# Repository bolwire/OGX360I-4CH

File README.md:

This project builds on the original OGX360 by Ryzee119: https://github.com/Ryzee119/ogx360/

The information provided in this repo is for informational purposes only.

The ATMEGA32U4 chips will need to be programmed with the arduino bootloader before they are put on the PCB. One option may be to remove the chips
from an arduino and transplant them.

Please respect the license files found within this project. What we do, and the joy we gain from that would not be possible without those who shared the
information with us to start with. Please respect and honor that by doing the same with any works derived from this or other projects linked to in this repo.

Also my spelling sucks, so I apologize for any type-ohs that exist.

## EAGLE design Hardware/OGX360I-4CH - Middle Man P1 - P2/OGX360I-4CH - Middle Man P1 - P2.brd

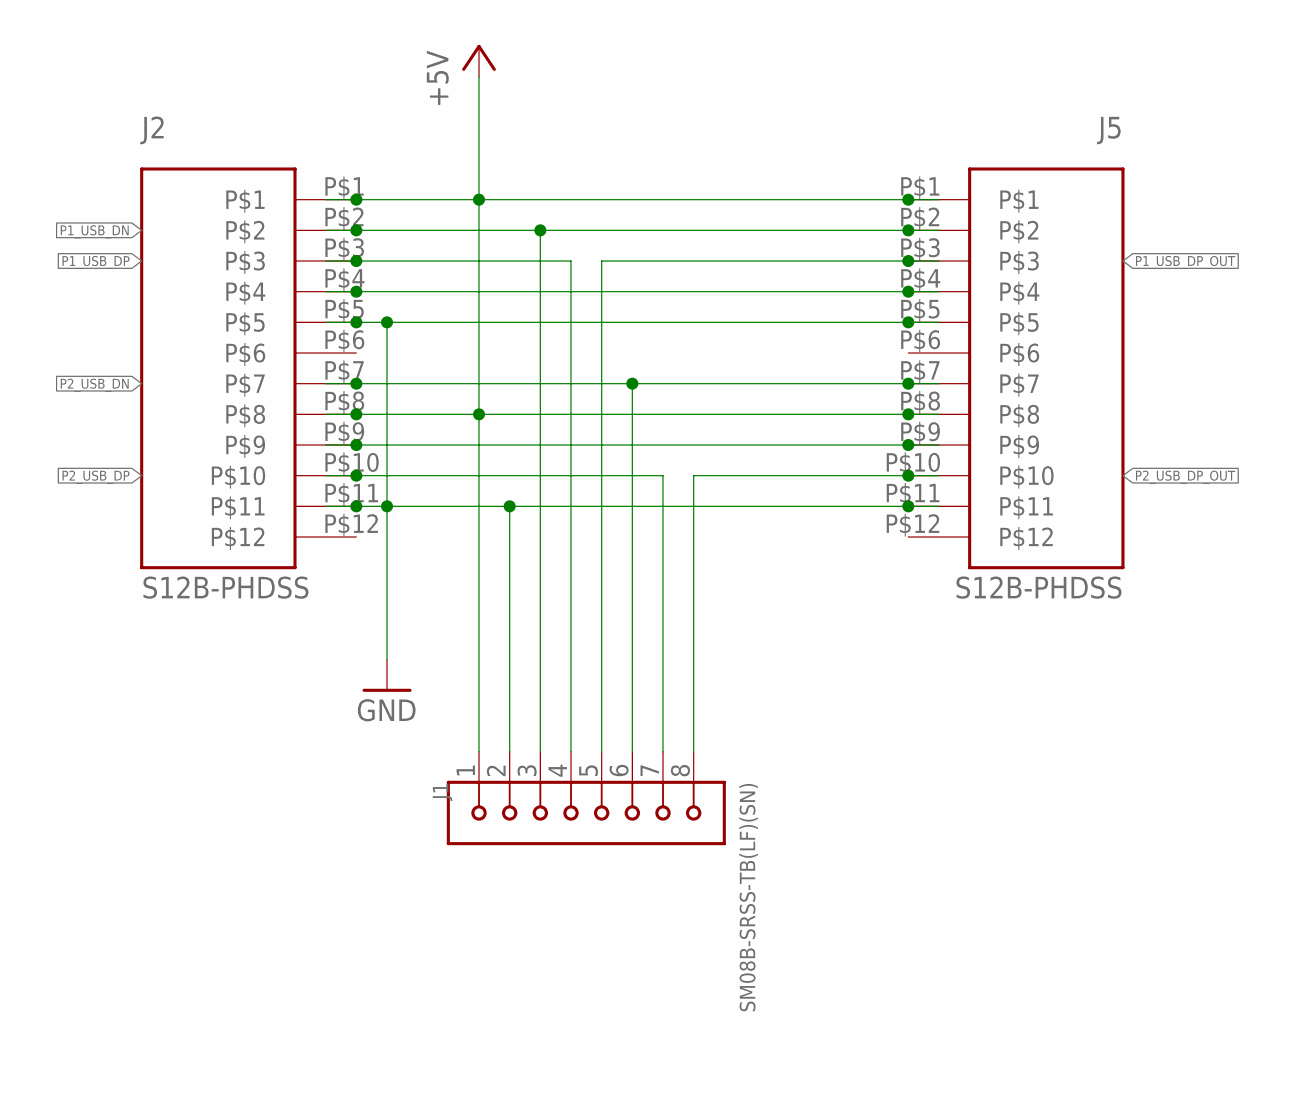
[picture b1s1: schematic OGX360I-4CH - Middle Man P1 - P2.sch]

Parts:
J1: SM08B-SRSS-TB(LF)(SN); JST_SM08B-SRSS-TB(LF)(SN)
J2, J5: S12B-PHDSS

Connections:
+5V: J1.1, J2.P$1, J2.P$8, J5.P$1, J5.P$8
GND: J1.2, J2.P$5, J2.P$11, J5.P$5, J5.P$11
unnamed: J2.P$4, J5.P$4
unnamed: J2.P$9, J5.P$9
P1_USB_DN: J1.3, J2.P$2, J5.P$2
P1_USB_DP: J1.4, J2.P$3
P1_USB_DP_OUT: J1.5, J5.P$3
P2_USB_DN: J1.6, J2.P$7, J5.P$7
P2_USB_DP: J1.7, J2.P$10
P2_USB_DP_OUT: J1.8, J5.P$10

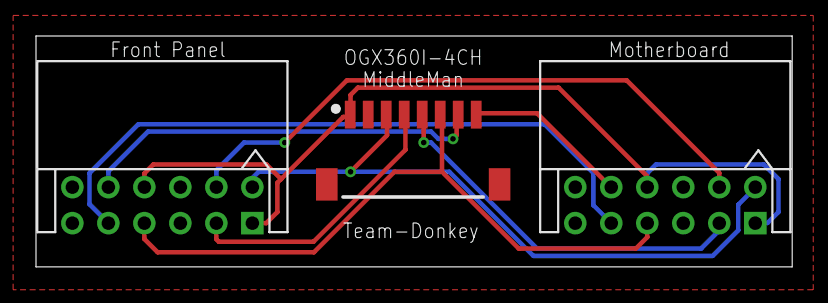
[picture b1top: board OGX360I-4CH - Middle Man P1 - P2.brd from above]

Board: 2 copper layers, 42.0 x 12.8 mm, 3 parts (0 on the bottom side), 10 nets.

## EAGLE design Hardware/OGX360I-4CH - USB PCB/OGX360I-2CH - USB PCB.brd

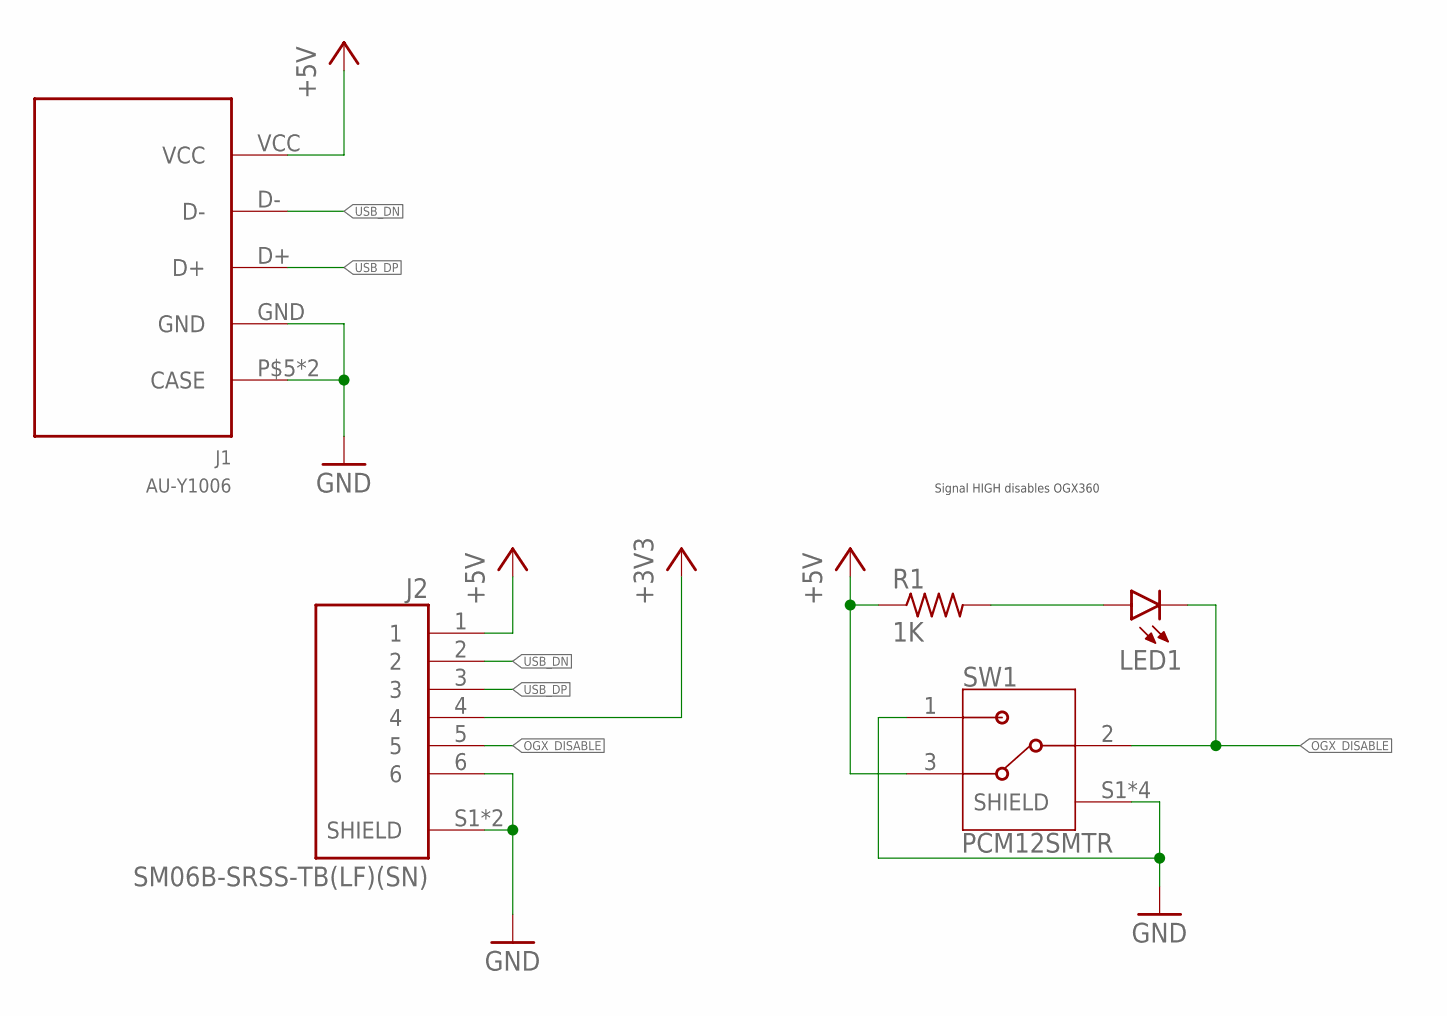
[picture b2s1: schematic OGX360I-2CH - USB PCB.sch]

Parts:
J1: AU-Y1006; USBA_SMD
J2: SM06B-SRSS-TB(LF)(SN); JST_SM06B-SRSS-TB(LF)(SN)
LED1: LEDCHIP-LED0805; CHIP-LED0805
R1: 1K; R0805
SW1: PCM12SMTR; SW_PCM12SMTR

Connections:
+3V3: J2.4
+5V: J1.VCC, J2.1, R1.1, SW1.3
GND: J1.GND, J1.P$5 (CASE), J1.P$6 (CASE), J2.6, J2.S1 (SHIELD), J2.S2 (SHIELD), SW1.1, SW1.S1 (SHIELD), SW1.S2 (SHIELD), SW1.S3 (SHIELD), SW1.S4 (SHIELD)
unnamed: LED1.A, R1.2
OGX_DISABLE: J2.5, LED1.C, SW1.2
USB_DN: J1.D-, J2.2
USB_DP: J1.D+, J2.3

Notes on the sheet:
Signal HIGH disables OGX360

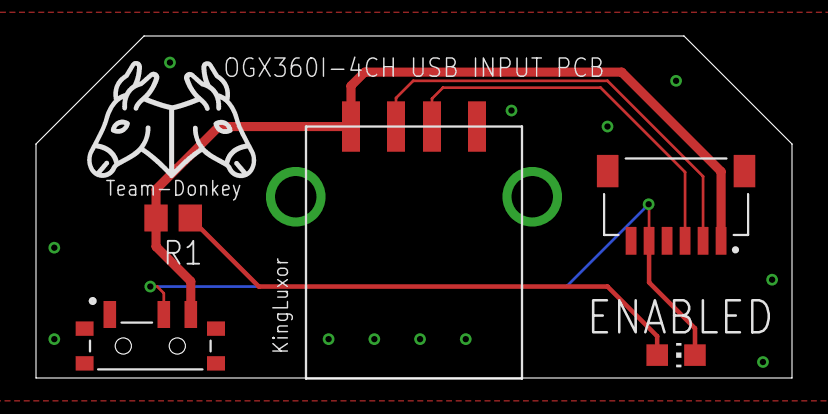
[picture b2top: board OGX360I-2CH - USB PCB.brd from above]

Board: 2 copper layers, 42.0 x 19.0 mm, 5 parts (0 on the bottom side), 6 nets.

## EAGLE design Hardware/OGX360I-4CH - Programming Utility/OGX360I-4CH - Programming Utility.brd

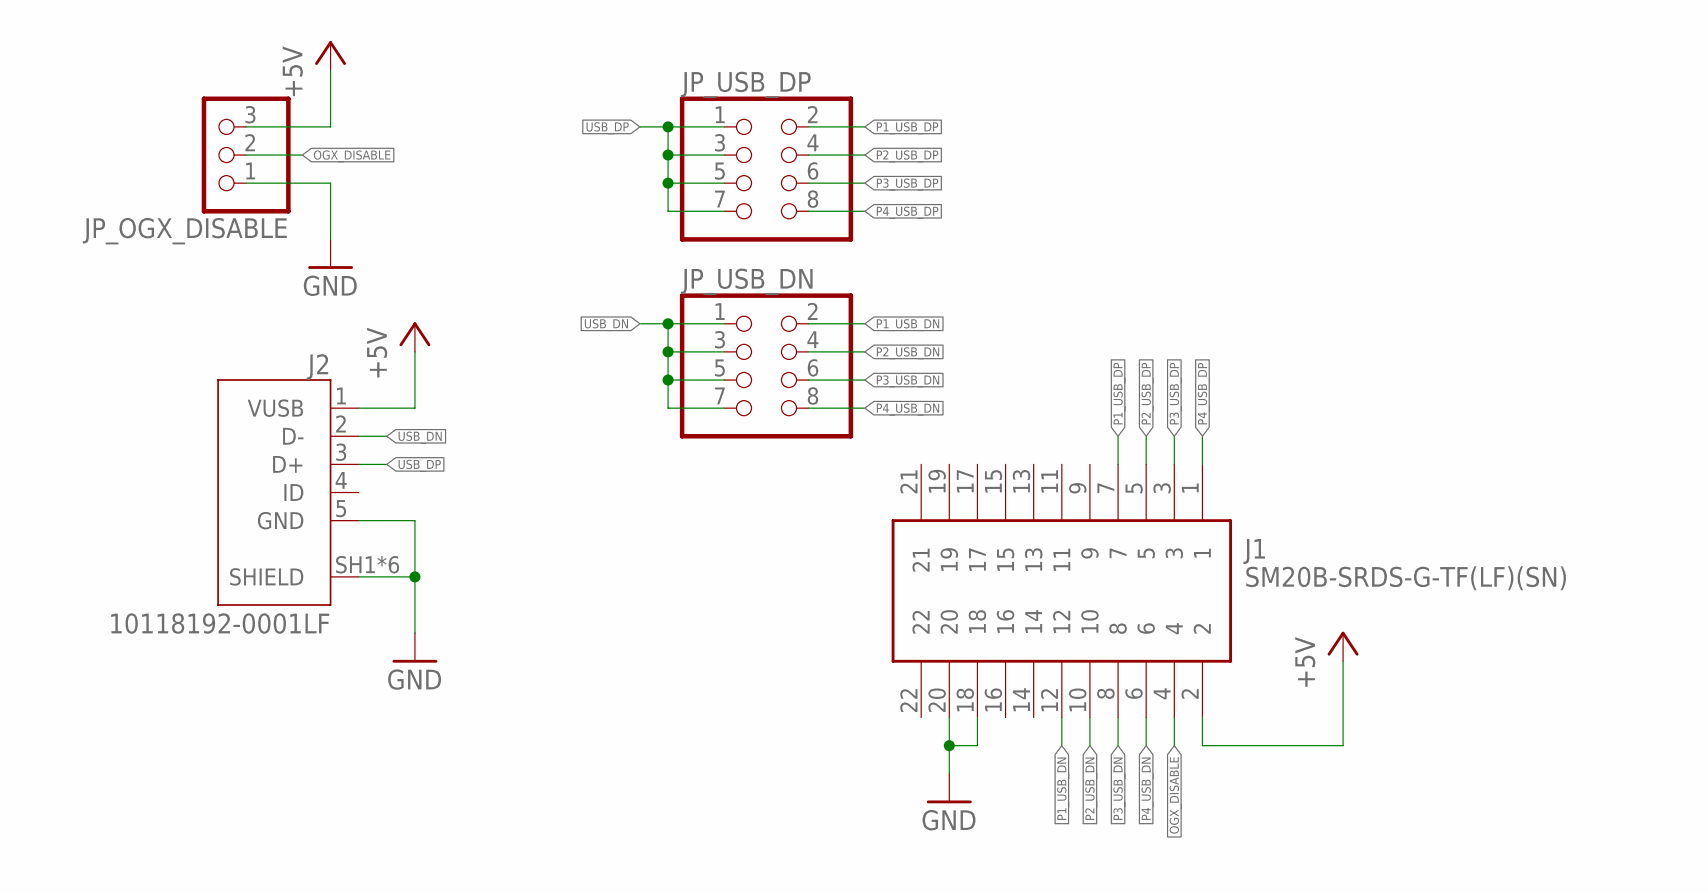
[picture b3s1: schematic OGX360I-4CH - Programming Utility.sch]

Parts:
J1: SM20B-SRDS-G-TF(LF)(SN); SM20BSRDSGTFLFSN
J2: 10118192-0001LF; AMPHENOL_10118192-0001LF
JP_OGX_DISABLE: PINHD-1X3; 1X03
JP_USB_DN: PINHD-2X4; 2X04
JP_USB_DP: PINHD-2X4; 2X04

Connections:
+5V: J1.2, J2.1 (VUSB), JP_OGX_DISABLE.3
GND: J1.18, J1.20, J2.5 (GND), J2.SH1 (SHIELD), J2.SH2 (SHIELD), J2.SH3 (SHIELD), J2.SH4 (SHIELD), J2.SH5 (SHIELD), J2.SH6 (SHIELD), JP_OGX_DISABLE.1
OGX_DISABLE: J1.4, JP_OGX_DISABLE.2
P1_USB_DN: J1.12, JP_USB_DN.2
P1_USB_DP: J1.7, JP_USB_DP.2
P2_USB_DN: J1.10, JP_USB_DN.4
P2_USB_DP: J1.5, JP_USB_DP.4
P3_USB_DN: J1.8, JP_USB_DN.6
P3_USB_DP: J1.3, JP_USB_DP.6
P4_USB_DN: J1.6, JP_USB_DN.8
P4_USB_DP: J1.1, JP_USB_DP.8
USB_DN: J2.2 (D-), JP_USB_DN.1, JP_USB_DN.3, JP_USB_DN.5, JP_USB_DN.7
USB_DP: J2.3 (D+), JP_USB_DP.1, JP_USB_DP.3, JP_USB_DP.5, JP_USB_DP.7

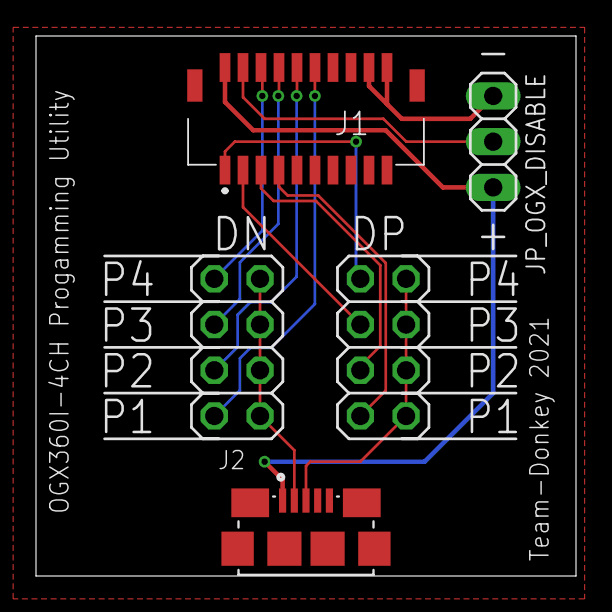
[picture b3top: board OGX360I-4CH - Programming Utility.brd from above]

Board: 2 copper layers, 30.0 x 30.0 mm, 5 parts (0 on the bottom side), 13 nets.

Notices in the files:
parts and their libraries:
SparkFun-Fuses: Licensing: Creative Commons ShareAlike 4.0 International - https://creativecommons.org/licenses/by-sa/4.0
